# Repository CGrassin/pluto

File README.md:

**Warning: This fork is a work in progress to replace the deprecated MAG3110 chip with the ST-LIS3MDL. Do not use, it is not ready.**

**Replacement software will be available on [Raphaël's repo](https://github.com/raphaelcasimir/pluto-fw)**

-----

Pluto is a programmable digital watch that re-uses case and LCD 
panel of the Casio® F-91W.  This is the hardware repo, for the 
software side of things, see [pluto-fw](https://github.com/carrotIndustries/pluto-fw).
Looking for pictures? [There you go.](photos/)
You can discuss the project and ask questions on the [EEVblog forum](http://www.eevblog.com/forum/oshw/diy-watch-based-on-the-casio-f-91w/)

# Features
- Displays time in decimal/binary/hexadecimal base
- Multiple alarms
- Multiple countdown timers
- Uses RTTTL ringtones for alarm sound
- Stopwatch
- Compass
- Speedometer (Enter distance, watch measures time and displays speed in km/h)
- Generation of time-based one-time passwords according to RFC 6238 (WIP)
- Menu-driven interface
- Infrared receiver for software updates and TOTP secret transfer (WIP)
- Useless customisation (Key beep frequency, etc.)
- greater than 1 year battery life (estimate based on current consumption)

# Hardware
Pluto replaces the PCB of the Casio F-91W with a custom one containing 
a MSP430FR6972 MCU, a digital magnetometer (compass) and a 38 kHz 
infrared receiver for software updates and communication. Due to 
careful planning and luck, the Pluto PCB perfectly fits inside of the 
F-91W's mounting frame, although it houses many more components.
[Schematic as PDF](f-91w.pdf) [BOM](f-91w.bom)
[BOM with Mouser part numbers](bom_mouser.txt)

## MCU
The MSP430FR6972 is a low-power 16bit MCU with integrated segment LCD 
controller. It can be programmed and debugged using the two-wire 
SBW interface accessible through holes in the mounting frame. 

## Digital Magnetometer
The ~~MAG3110~~LIS3MDL compass is connected to the MCU via I²C. To reduce its power 
consumption to zero when not in use, it's powered from GPIO pin. Due to 
layout constraints, the MCU's I²C interface can't be used, so the 
MCU's firmware has to implement a bit-banged I²C master controller.

## Infrared Receiver
The TSOP57338 38kHz IR receiver is powered from GPIO pin as well since 
it doesn't have any power saving modes. Transmitter and firmware 
support are WIP.

## Other components
The backlight LED is connected to two GPIO pins, so that LEDs of either 
orientation can be fitted.
The driving circuit for the buzzer uses an inductor (measured approx. 
10mH) to boost the battery voltage for increased volume.

## PCB
We manufactured the PCB at [elecrow](http://www.elecrow.com). PCB 
thickness has to be 0.6mm for the PCB to fit between battery clip and plastic 
frame. Note that the PCB has "castellated vias" (for contacting the 
button springs) as PCB manufacturers usually surcharge for these. We 
chose to use ENIG (gold) finish since the original PCB is gold-plated 
as well and Casio wouldn't have done so if this wasn't strictly 
necessary. Unfortunately, not all vias are covered with solder mask due 
manufacturing details (in the gerber files, they are), so you'll have 
to insulate the bottom side of the PCB from the battery with sticky 
tape.

# Software
For details on the software, see the software repository at 
[pluto-fw](https://github.com/carrotIndustries/pluto-fw).

# Why?
I used to own an ez430-Chronos watch, but after several years of use, 
the rubber wrist strap disintegrated, so I needed a new programmable watch. 
Pretty much all of the existing DIY watches are impractical for daily 
use because of bulk, being not waterproof or having miserable battery 
life. 

# PAQ (Possibly asked questions)
Q: Why not just use a smartwatch?  
A: Smartwatches have a miserable battery life of one week at best. Some 
even require user interaction to display the time.

Q: Why isn't there some sort of radio interface? (BLE, nRF24L01)  
A: Take look at [this](photos#perfect-fit) picture to get an idea of the space available 
inside of the F-91W frame. The nRF24L01 is 4 mm×4 mm and barely fits, but 
requires external components like balun and antenna. There's no space 
for these. An IR receiver is the same size as the nRF24L01, but doesn't 
require any external components. TI's CC430 MCUs seem like a perfect 
match for pluto as since they combine MCU and radio, but since the radio operates at 
sub-1GHz frequency, the antenna needs to be prohibitively large.

Q: Why is there no accelerometer?  
A: Accelerometers are the most useful when they're permanently active 
for applications like sleep trackers, pedometers or features like 
"shake to do something". Unfortunately, even accelerometers marketed as
"ultralow power" draw approx 30 µA when running, draining the CR2016
coin cell in less than half a year.  So we decided to dedicate the 
available space to a digital compass.

# Credits
Thanks go to [sh-ow](https://github.com/sh-ow) for adding the compass 
and helping to get the board ready for manufacturing.

# Mixed bag
Stuff loosely related to this project

## Reverse Engineering bare glass LCD panels
For basics on bare glass LCD panels and how to drive them,
see application notes from various MCU vendors.

For driving an unknown LCD panel, one needs to know which 
pins connect to the backplanes (COM) and which ones connect to segments 
(SEG). The easiest way to do so is to apply a square to all pins of the 
LCD panel and invert one pin at a time. When few segments light up, 
you've got a SEG pin, when many light up, you've got a COM pin. 
Sometimes apparently independent LCD segments are driven as one segment 
to save SEG pins. 

## Reverse engineering intricate PCB outlines
The F91-W's original PCB has a rather complicated outline that needs to 
be duplicated with high precision, so that the Pluto PCB fits nicely 
within the existing mounting frame.

By desoldering the spring contacting the piezo buzzer, the PCB is 
completely flat on the bottom side, so it can be placed on a flat-bed 
scanner. This eliminates any kind of distortion you'd get by taking a 
photo. The scanned image can then be scaled to match the actual 
dimensions measured with a caliper. There may be unequal scaling in X 
and Y direction due to inaccuracies of the scanner. We've now got a 
pretty accurate digital representation of the PCB that can be used for 
tracing out the outline and registering photos from the top side of 
the PCB to get the position of pads on top side.

Inkscape and GIMP (for correcting camera distortion) work well for 
these tasks. The resulting outline has been exported as a dxf document 
for importing the outline in KiCad.

## Things that didn't work out
The project started off with the intent of re-purposing the the F-91W 
case and LCD. Unfortunately, the LCD panel of the F-91W is rather 
limited since some LCD segments are driven as one segment.

So we went out and took a look at the Casio W800, F-201 and DB-36 
watch. After manufacturing a test jig for the LCD panels of the former 
two, it turned out that people at Casio /really/ like building LCDs 
with 5 backplanes. For some reason, the LCD panels need also to be driven 
with around 5 Vpp to achieve decent contrast. (Best guess: These 
watches are old designs, LCDs weren't that sensitive back then)

To my best knowledge, there's no (non-unobtainium) MCU on the market, 
that can boost a 3 V supply to 5 V for driving and LCDs /and/ can do 
5-mux. The only MCUs meeting the first requirement are from the RL78 
family from Renesas, but they only do 1,2,3,4 and 8-mux. Driving a 5-mux LCD 
with 8-mux waveforms leads to bad contrast. With 3 V and 5-mux, the contrast is 
much worse.

EPSON offers some obscure MCUs that can do both 5-mux and 
5 V LCD drive, but these ones don't have enough segment pins the QFN64 
package.

So we went back to F-91W.

## Measuring current consumption
For plotting current consumption over time, the EnergyTrace feature of 
the MSP430FR4133 LaunchPad has proven to be really useful: 
[energytrace-util](https://github.com/carrotIndustries/energytrace-util)

## Related Projects
Looking for more buttons and a radio? Take a look at [goodwatch](https://github.com/travisgoodspeed/goodwatch/)

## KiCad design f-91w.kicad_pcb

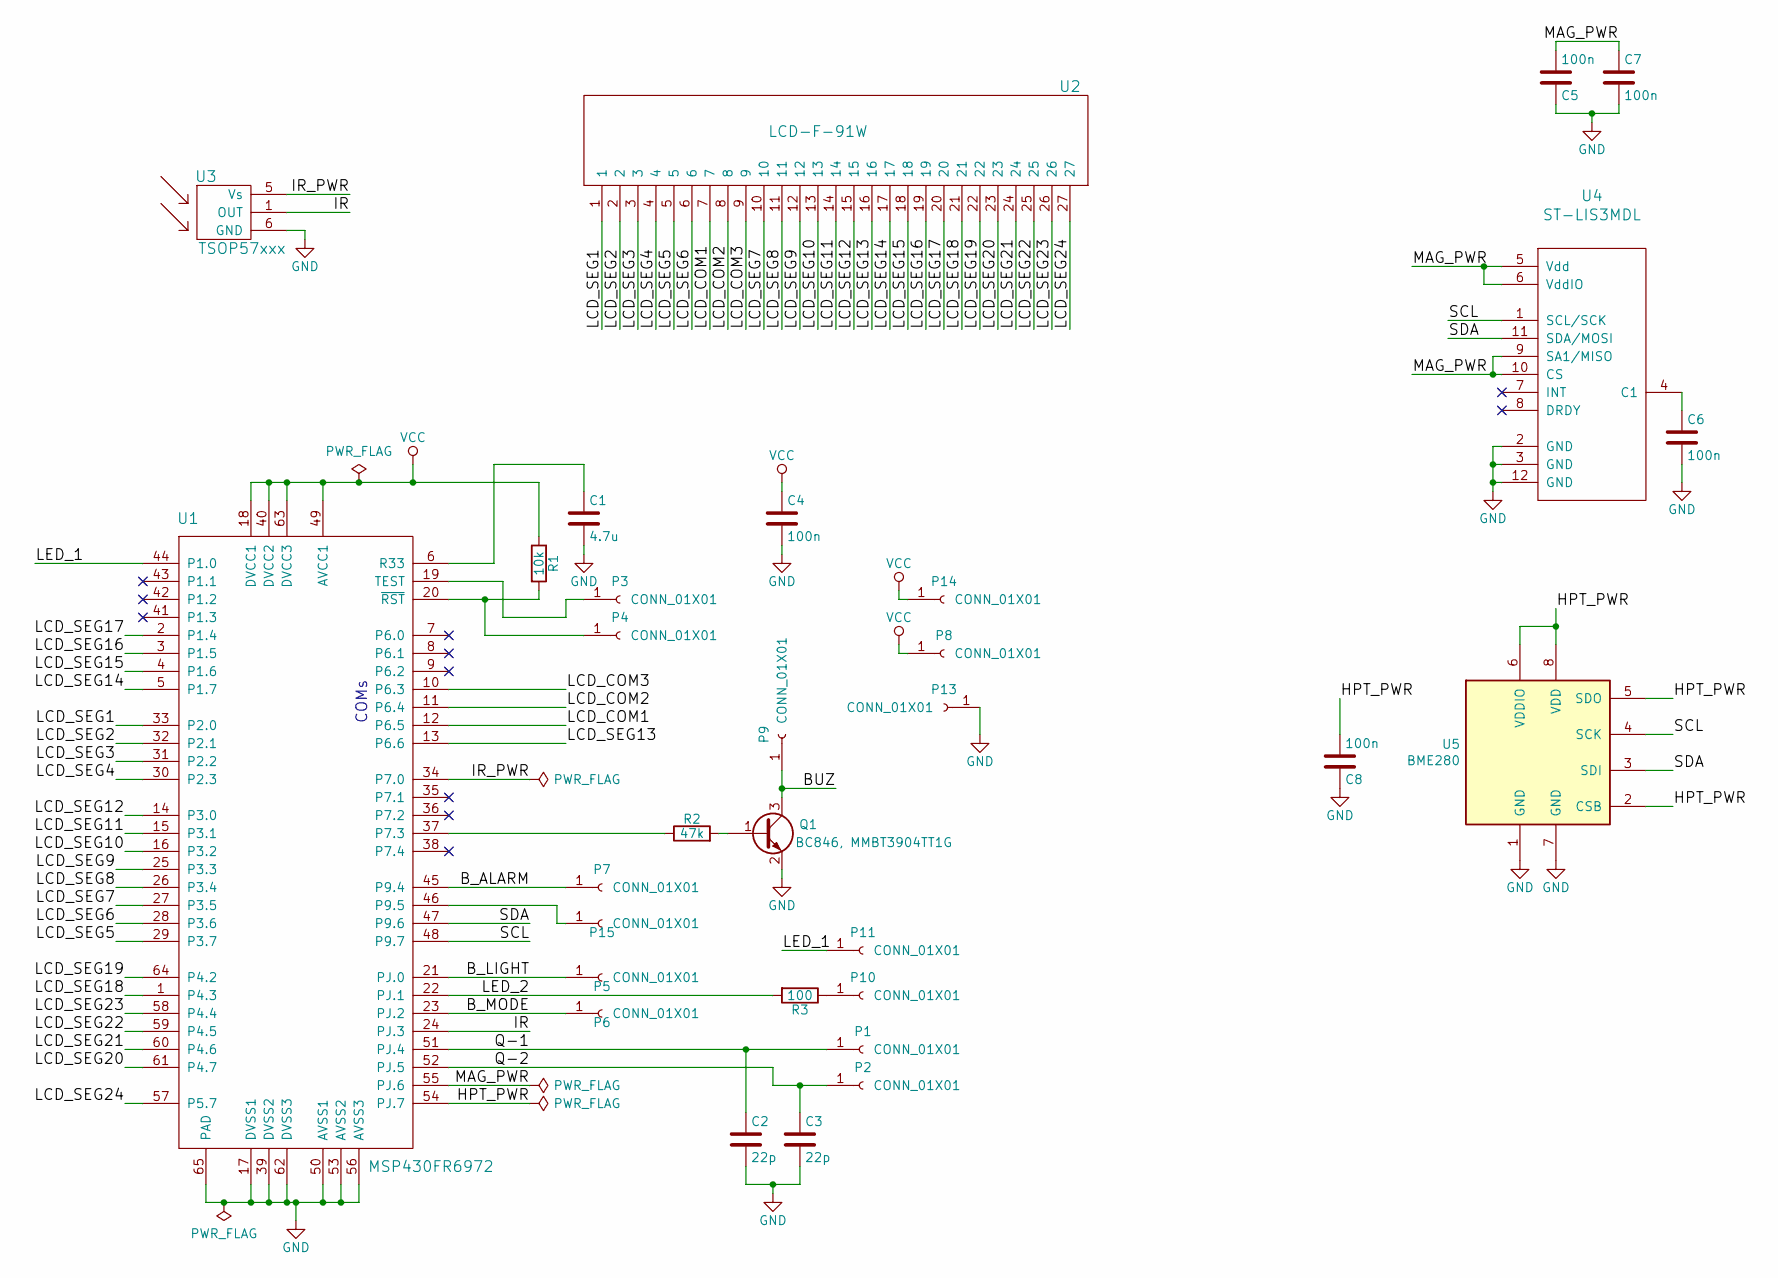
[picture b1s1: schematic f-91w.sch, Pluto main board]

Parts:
C1: 4.7u; C_0402_1005Metric
C2, C3: 22p; C_0402_1005Metric
C4, C5, C6, C7, C8: 100n; C_0402_1005Metric
P1, P2, P3, P4, P5, P6, P7, P8, P9, P10, P11, P13, P14, P15: CONN_01X01; 1pin
Q1: BC846, MMBT3904TT1G; SOT-416
R1: 10k; R_0402_1005Metric
R2: 47k; R_0402_1005Metric
R3: 100; R_0402_1005Metric
U1: MSP430FR6972; QFN-64-1EP_9x9mm_P0.5mm_EP7.3x7.3mm
U2: LCD-F-91W
U3: TSOP57xxx
U4: ST-LIS3MDL; LGA-12_2x2mm_P0.5mm
U5: BME280; Bosch_LGA-8_2.5x2.5mm_P0.65mm_ClockwisePinNumbering

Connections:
/BUZ: P9.1, Q1.3 (C)
/B_ALARM: P7.1, U1.45 (P9.4)
/B_LIGHT: P5.1, U1.21 (PJ.0)
/B_MODE: P6.1, U1.23 (PJ.2)
/HPT_PWR: C8.2, U1.54 (PJ.7), U5.2 (CSB), U5.5 (SDO), U5.6 (VDDIO), U5.8 (VDD)
/IR: U1.24 (PJ.3), U3.1 (OUT)
/IR_PWR: U1.34 (P7.0), U3.5 (Vs)
/LCD_COM1: U1.12 (P6.5), U2.7
/LCD_COM2: U1.11 (P6.4), U2.8
/LCD_COM3: U1.10 (P6.3), U2.9
/LCD_SEG1: U1.33 (P2.0), U2.1
/LCD_SEG2: U1.32 (P2.1), U2.2
/LCD_SEG3: U1.31 (P2.2), U2.3
/LCD_SEG4: U1.30 (P2.3), U2.4
/LCD_SEG5: U1.29 (P3.7), U2.5
/LCD_SEG6: U1.28 (P3.6), U2.6
/LCD_SEG7: U1.27 (P3.5), U2.10
/LCD_SEG8: U1.26 (P3.4), U2.11
/LCD_SEG9: U1.25 (P3.3), U2.12
/LCD_SEG10: U1.16 (P3.2), U2.13
/LCD_SEG11: U1.15 (P3.1), U2.14
/LCD_SEG12: U1.14 (P3.0), U2.15
/LCD_SEG13: U1.13 (P6.6), U2.16
/LCD_SEG14: U1.5 (P1.7), U2.17
/LCD_SEG15: U1.4 (P1.6), U2.18
/LCD_SEG16: U1.3 (P1.5), U2.19
/LCD_SEG17: U1.2 (P1.4), U2.20
/LCD_SEG18: U1.1 (P4.3), U2.21
/LCD_SEG19: U1.64 (P4.2), U2.22
/LCD_SEG20: U1.61 (P4.7), U2.23
/LCD_SEG21: U1.60 (P4.6), U2.24
/LCD_SEG22: U1.59 (P4.5), U2.25
/LCD_SEG23: U1.58 (P4.4), U2.26
/LCD_SEG24: U1.57 (P5.7), U2.27
/LED_1: P11.1, U1.44 (P1.0)
/LED_2: R3.2, U1.22 (PJ.1)
/MAG_PWR: C5.2, C7.1, U1.55 (PJ.6), U4.5 (Vdd), U4.6 (VddIO), U4.9 (SA1/MISO), U4.10 (CS)
/Q-1: C2.1, P1.1, U1.51 (PJ.4)
/Q-2: C3.1, P2.1, U1.52 (PJ.5)
/SCL: U1.48 (P9.7), U4.1 (SCL/SCK), U5.4 (SCK)
/SDA: U1.47 (P9.6), U4.11 (SDA/MOSI), U5.3 (SDI)
GND: C1.2, C2.2, C3.2, C4.2, C5.1, C6.2, C7.2, C8.1, P13.1, Q1.2 (E), U1.17 (DVSS1), U1.39 (DVSS2), U1.50 (AVSS1), U1.53 (AVSS2), U1.56 (AVSS3), U1.62 (DVSS3), U1.65 (PAD), U3.6 (GND), U4.2 (GND), U4.3 (GND), U4.12 (GND), U5.1 (GND), U5.7 (GND)
unnamed: C1.1, U1.6 (R33)
unnamed: C6.1, U4.4 (C1)
unnamed: P3.1, U1.19 (TEST)
unnamed: P4.1, R1.2, U1.20 (~RST)
unnamed: P10.1, R3.1
unnamed: P15.1, U1.46 (P9.5)
unnamed: Q1.1 (B), R2.2
unnamed: R2.1, U1.37 (P7.3)
VCC: C4.1, P8.1, P14.1, R1.1, U1.18 (DVCC1), U1.40 (DVCC2), U1.49 (AVCC1), U1.63 (DVCC3)

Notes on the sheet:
COMs

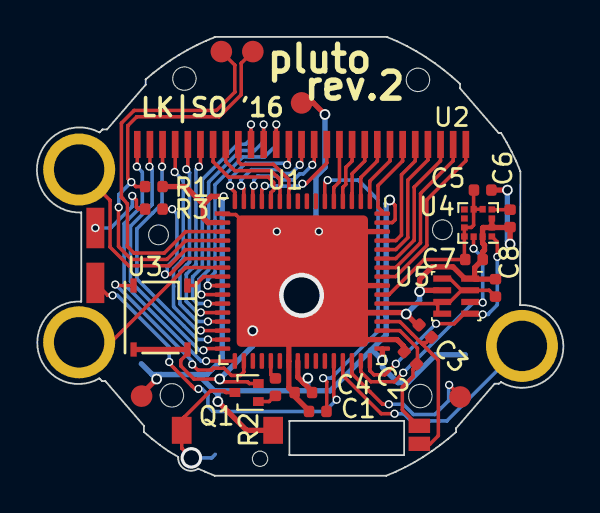
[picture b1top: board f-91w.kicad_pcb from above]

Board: 2 copper layers, 29.3 x 24.4 mm, 38 parts (0 on the bottom side), 51 nets.

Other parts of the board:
MH1, MH2, MH3, MH4, MH5, MH6, MH7: 1pin

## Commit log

2019-05-05 Changed MAG3110 magnetometer to ST-LIS3MDL, made project compatible with Kicad 5 libraries
2019-05-05 Added PCB rendering
2019-05-05 Changed rendering image
2019-05-05 Added Gerber files
2019-05-05 Added interactive BOM
2019-05-05 Added alternative NPN part
2019-05-05 Added alternative NPN part (fixed)
2019-05-05 Added board cut ears to remove the need for castellated holes
2019-05-05 Updated BOM and gerber
2019-05-05 Updated gerber
2019-05-05 Added origin of PCB
2019-05-05 Added origin of PCB (fixed)
2019-05-05 Minor PCB changes
2019-05-06 Updated rendering to last PCB version and added hackaday black version
2019-05-10 Added the BME280 or BMP280 sensor
